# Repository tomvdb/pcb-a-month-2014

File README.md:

PCB a Month 2014
================

Design files for my PCB A Month 2014 Project

January:

BinarySpace Valentine Flower Project (Tested 13 Feb 2014)

February

Battery Charger Experiment Board (Not Tested Yet)

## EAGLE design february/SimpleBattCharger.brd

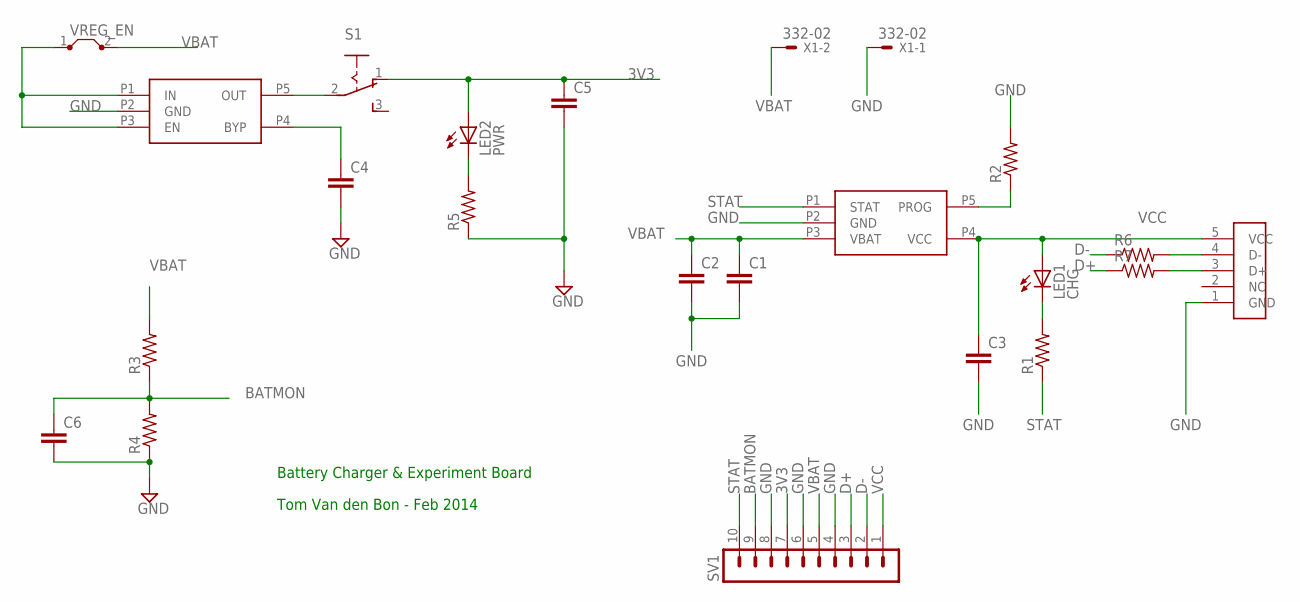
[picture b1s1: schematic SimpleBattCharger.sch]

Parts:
C1, C2, C3: C-EUC0603K; C0603K
C4, C6: C-EUC0603; C0603
C5: C-EUC3225; C3225
LED1: CHG; SML0603
LED2: PWR; SML0603
R1, R2, R3, R4, R5, R6, R7: R-US_R0603; R0603
S1: 255SB
SV1: MA10-1
U$1: USBSOCK_MINI_SMD
U$2: MCP73831MCP73831T-2ACI/OT; SOT-23-5
U$3: MIC5219-X.XBM5MIC5219-3.3YM5TR; SOT-23-5
VREG_EN: J5MM; 05
X1: 332-02

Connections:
3V3: C5.1, LED2.A, S1.1 (O), SV1.7
BATMON: C6.1, R3.1, R4.2, SV1.9
D+: R7.1, SV1.3
D-: R6.1, SV1.2
GND: C1.2, C2.2, C3.2, C4.2, C5.2, C6.2, R2.2, R4.1, R5.1, SV1.4, SV1.6, SV1.8, U$1.1 (GND), U$2.P2 (GND), U$3.P2 (GND), X1.1
unnamed: R2.1, U$2.P5 (PROG)
unnamed: LED1.C, R1.2
unnamed: C4.1, U$3.P4 (BYP)
unnamed: U$3.P1 (IN), U$3.P3 (EN), VREG_EN.1
unnamed: S1.2, U$3.P5 (OUT)
unnamed: LED2.C, R5.2
unnamed: R6.2, U$1.4 (D-)
unnamed: R7.2, U$1.3 (D+)
STAT: R1.1, SV1.10, U$2.P1 (STAT)
VBAT: C1.1, C2.1, R3.2, SV1.5, U$2.P3 (VBAT), VREG_EN.2, X1.2
VCC: C3.1, LED1.A, SV1.1, U$1.5 (VCC), U$2.P4 (VCC)

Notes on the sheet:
Battery Charger & Experiment Board
Tom Van den Bon - Feb 2014

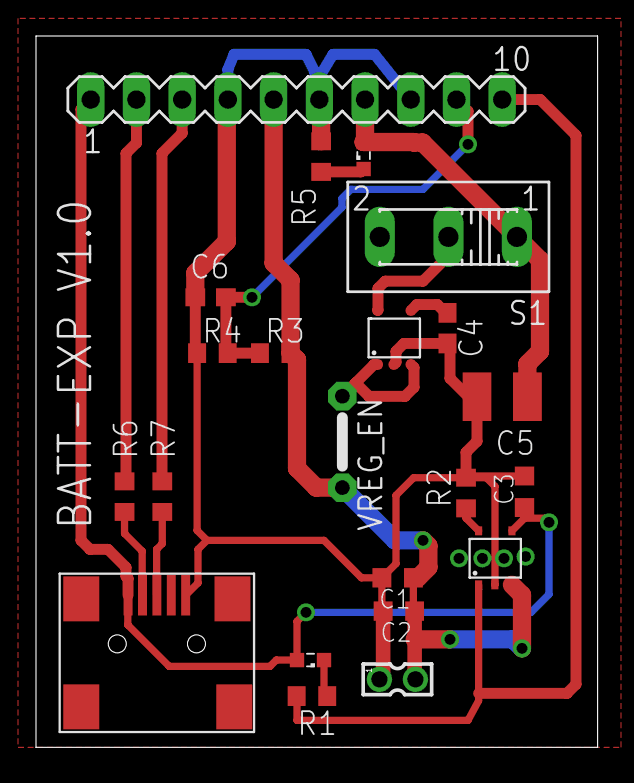
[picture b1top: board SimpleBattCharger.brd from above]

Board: 2 copper layers, 31.2 x 39.5 mm, 22 parts (0 on the bottom side), 16 nets.

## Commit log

2014-03-17 added february board
